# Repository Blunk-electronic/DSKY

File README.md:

# DSKY
is a I²C controlled 8 digit display and keypad unit

some images:

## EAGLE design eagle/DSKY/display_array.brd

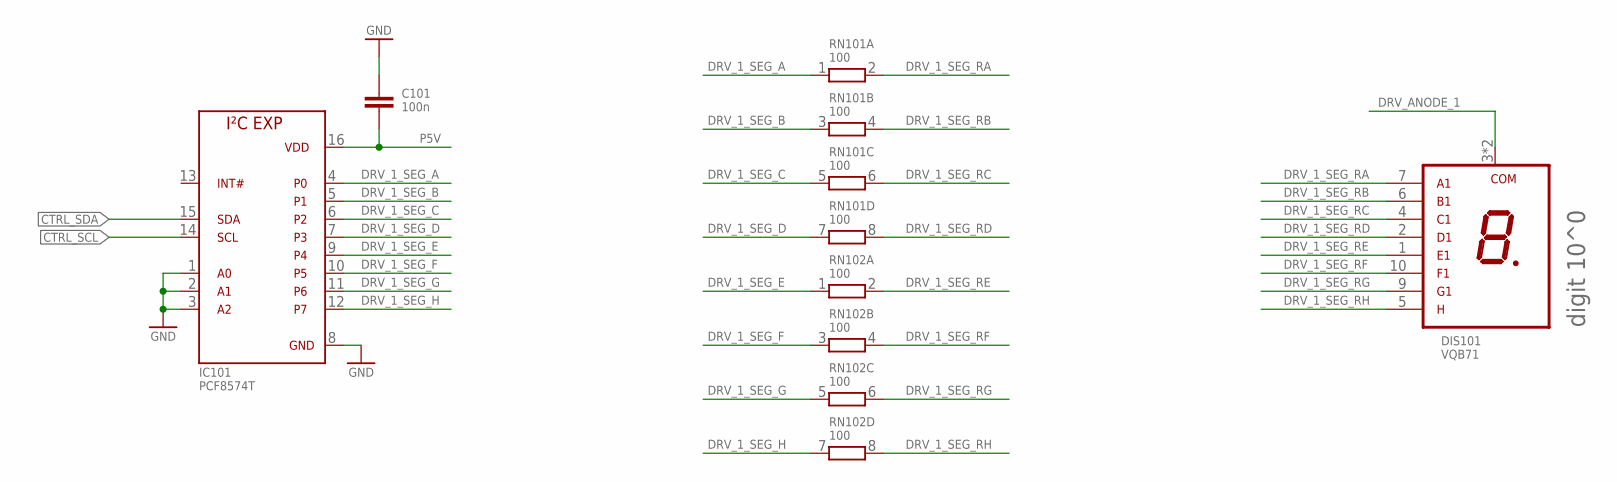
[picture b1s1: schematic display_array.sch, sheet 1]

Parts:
C101: 100n; S_0805; PART_CODE_BEL C_PAC_S_0805_VAL_100n
DIS101: VQB71; T_VQB71
IC101: PCF8574T; S_SOIC16
RN101, RN102: 100; T_SIL8; PART_CODE_BEL RN_PAC_T_SIL8_VAL_100

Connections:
CTRL_SCL: IC101.14 (SCL); also elsewhere on the board
CTRL_SDA: IC101.15 (SDA); also elsewhere on the board
DRV_1_SEG_A: IC101.4 (P0), RN101.1
DRV_1_SEG_B: IC101.5 (P1), RN101.3 (1)
DRV_1_SEG_C: IC101.6 (P2), RN101.5 (1)
DRV_1_SEG_D: IC101.7 (P3), RN101.7 (1)
DRV_1_SEG_E: IC101.9 (P4), RN102.1
DRV_1_SEG_F: IC101.10 (P5), RN102.3 (1)
DRV_1_SEG_G: IC101.11 (P6), RN102.5 (1)
DRV_1_SEG_H: IC101.12 (P7), RN102.7 (1)
DRV_1_SEG_RA: DIS101.7 (A1), RN101.2
DRV_1_SEG_RB: DIS101.6 (B1), RN101.4 (2)
DRV_1_SEG_RC: DIS101.4 (C1), RN101.6 (2)
DRV_1_SEG_RD: DIS101.2 (D1), RN101.8 (2)
DRV_1_SEG_RE: DIS101.1 (E1), RN102.2
DRV_1_SEG_RF: DIS101.10 (F1), RN102.4 (2)
DRV_1_SEG_RG: DIS101.9 (G1), RN102.6 (2)
DRV_1_SEG_RH: DIS101.5 (DP1), RN102.8 (2)
DRV_ANODE_1: DIS101.3 (COM1), DIS101.8 (COM1); also elsewhere on the board
GND: C101.1, IC101.1 (A0), IC101.2 (A1), IC101.3 (A2), IC101.8 (GND); also elsewhere on the board
P5V: C101.2, IC101.16 (VDD); also elsewhere on the board

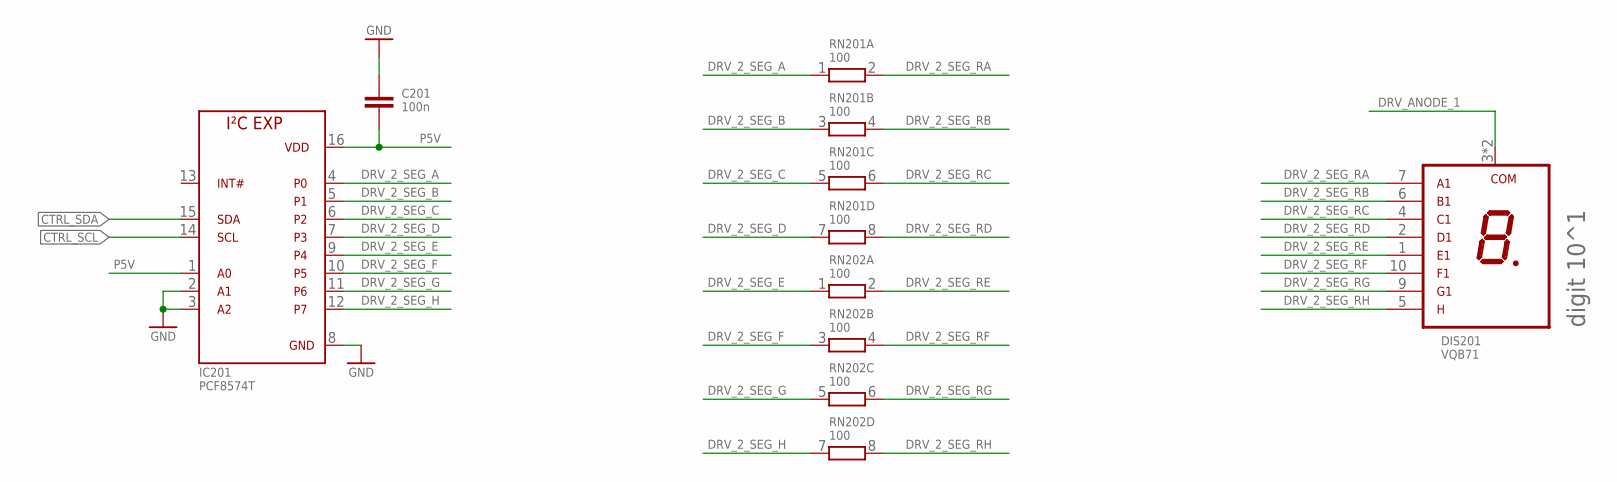
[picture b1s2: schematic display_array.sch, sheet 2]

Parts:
C201: 100n; S_0805; PART_CODE_BEL C_PAC_S_0805_VAL_100n
DIS201: VQB71; T_VQB71
IC201: PCF8574T; S_SOIC16
RN201, RN202: 100; T_SIL8; PART_CODE_BEL RN_PAC_T_SIL8_VAL_100

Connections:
CTRL_SCL: IC201.14 (SCL); also elsewhere on the board
CTRL_SDA: IC201.15 (SDA); also elsewhere on the board
DRV_2_SEG_A: IC201.4 (P0), RN201.1
DRV_2_SEG_B: IC201.5 (P1), RN201.3 (1)
DRV_2_SEG_C: IC201.6 (P2), RN201.5 (1)
DRV_2_SEG_D: IC201.7 (P3), RN201.7 (1)
DRV_2_SEG_E: IC201.9 (P4), RN202.1
DRV_2_SEG_F: IC201.10 (P5), RN202.3 (1)
DRV_2_SEG_G: IC201.11 (P6), RN202.5 (1)
DRV_2_SEG_H: IC201.12 (P7), RN202.7 (1)
DRV_2_SEG_RA: DIS201.7 (A1), RN201.2
DRV_2_SEG_RB: DIS201.6 (B1), RN201.4 (2)
DRV_2_SEG_RC: DIS201.4 (C1), RN201.6 (2)
DRV_2_SEG_RD: DIS201.2 (D1), RN201.8 (2)
DRV_2_SEG_RE: DIS201.1 (E1), RN202.2
DRV_2_SEG_RF: DIS201.10 (F1), RN202.4 (2)
DRV_2_SEG_RG: DIS201.9 (G1), RN202.6 (2)
DRV_2_SEG_RH: DIS201.5 (DP1), RN202.8 (2)
DRV_ANODE_1: DIS201.3 (COM1), DIS201.8 (COM1); also elsewhere on the board
GND: C201.1, IC201.2 (A1), IC201.3 (A2), IC201.8 (GND); also elsewhere on the board
P5V: C201.2, IC201.1 (A0), IC201.16 (VDD); also elsewhere on the board

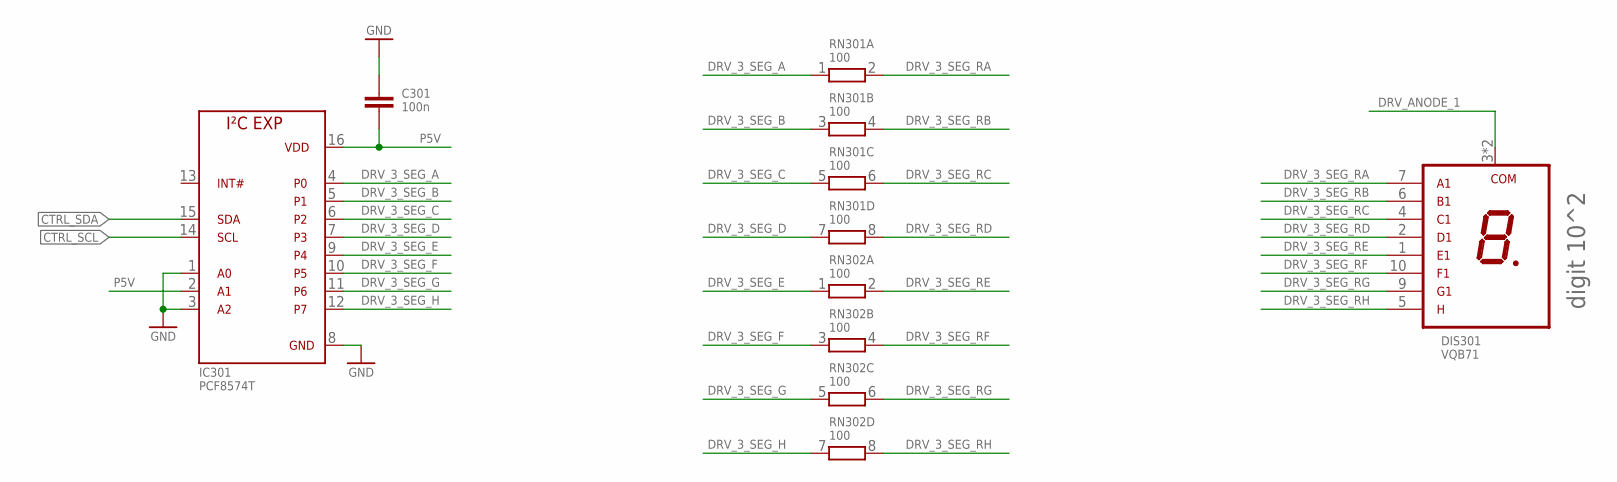
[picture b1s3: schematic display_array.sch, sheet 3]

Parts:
C301: 100n; S_0805; PART_CODE_BEL C_PAC_S_0805_VAL_100n
DIS301: VQB71; T_VQB71
IC301: PCF8574T; S_SOIC16
RN301, RN302: 100; T_SIL8; PART_CODE_BEL RN_PAC_T_SIL8_VAL_100

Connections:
CTRL_SCL: IC301.14 (SCL); also elsewhere on the board
CTRL_SDA: IC301.15 (SDA); also elsewhere on the board
DRV_3_SEG_A: IC301.4 (P0), RN301.1
DRV_3_SEG_B: IC301.5 (P1), RN301.3 (1)
DRV_3_SEG_C: IC301.6 (P2), RN301.5 (1)
DRV_3_SEG_D: IC301.7 (P3), RN301.7 (1)
DRV_3_SEG_E: IC301.9 (P4), RN302.1
DRV_3_SEG_F: IC301.10 (P5), RN302.3 (1)
DRV_3_SEG_G: IC301.11 (P6), RN302.5 (1)
DRV_3_SEG_H: IC301.12 (P7), RN302.7 (1)
DRV_3_SEG_RA: DIS301.7 (A1), RN301.2
DRV_3_SEG_RB: DIS301.6 (B1), RN301.4 (2)
DRV_3_SEG_RC: DIS301.4 (C1), RN301.6 (2)
DRV_3_SEG_RD: DIS301.2 (D1), RN301.8 (2)
DRV_3_SEG_RE: DIS301.1 (E1), RN302.2
DRV_3_SEG_RF: DIS301.10 (F1), RN302.4 (2)
DRV_3_SEG_RG: DIS301.9 (G1), RN302.6 (2)
DRV_3_SEG_RH: DIS301.5 (DP1), RN302.8 (2)
DRV_ANODE_1: DIS301.3 (COM1), DIS301.8 (COM1); also elsewhere on the board
GND: C301.1, IC301.1 (A0), IC301.3 (A2), IC301.8 (GND); also elsewhere on the board
P5V: C301.2, IC301.2 (A1), IC301.16 (VDD); also elsewhere on the board

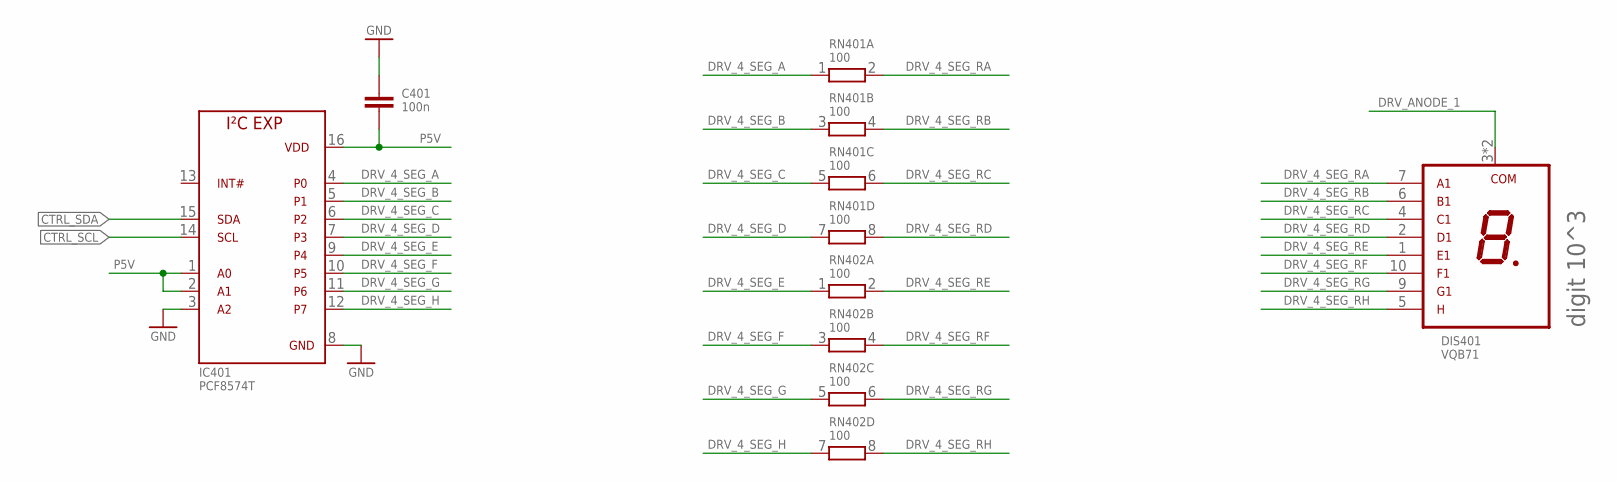
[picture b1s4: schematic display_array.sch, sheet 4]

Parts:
C401: 100n; S_0805; PART_CODE_BEL C_PAC_S_0805_VAL_100n
DIS401: VQB71; T_VQB71
IC401: PCF8574T; S_SOIC16
RN401, RN402: 100; T_SIL8; PART_CODE_BEL RN_PAC_T_SIL8_VAL_100

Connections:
CTRL_SCL: IC401.14 (SCL); also elsewhere on the board
CTRL_SDA: IC401.15 (SDA); also elsewhere on the board
DRV_4_SEG_A: IC401.4 (P0), RN401.1
DRV_4_SEG_B: IC401.5 (P1), RN401.3 (1)
DRV_4_SEG_C: IC401.6 (P2), RN401.5 (1)
DRV_4_SEG_D: IC401.7 (P3), RN401.7 (1)
DRV_4_SEG_E: IC401.9 (P4), RN402.1
DRV_4_SEG_F: IC401.10 (P5), RN402.3 (1)
DRV_4_SEG_G: IC401.11 (P6), RN402.5 (1)
DRV_4_SEG_H: IC401.12 (P7), RN402.7 (1)
DRV_4_SEG_RA: DIS401.7 (A1), RN401.2
DRV_4_SEG_RB: DIS401.6 (B1), RN401.4 (2)
DRV_4_SEG_RC: DIS401.4 (C1), RN401.6 (2)
DRV_4_SEG_RD: DIS401.2 (D1), RN401.8 (2)
DRV_4_SEG_RE: DIS401.1 (E1), RN402.2
DRV_4_SEG_RF: DIS401.10 (F1), RN402.4 (2)
DRV_4_SEG_RG: DIS401.9 (G1), RN402.6 (2)
DRV_4_SEG_RH: DIS401.5 (DP1), RN402.8 (2)
DRV_ANODE_1: DIS401.3 (COM1), DIS401.8 (COM1); also elsewhere on the board
GND: C401.1, IC401.3 (A2), IC401.8 (GND); also elsewhere on the board
P5V: C401.2, IC401.1 (A0), IC401.2 (A1), IC401.16 (VDD); also elsewhere on the board

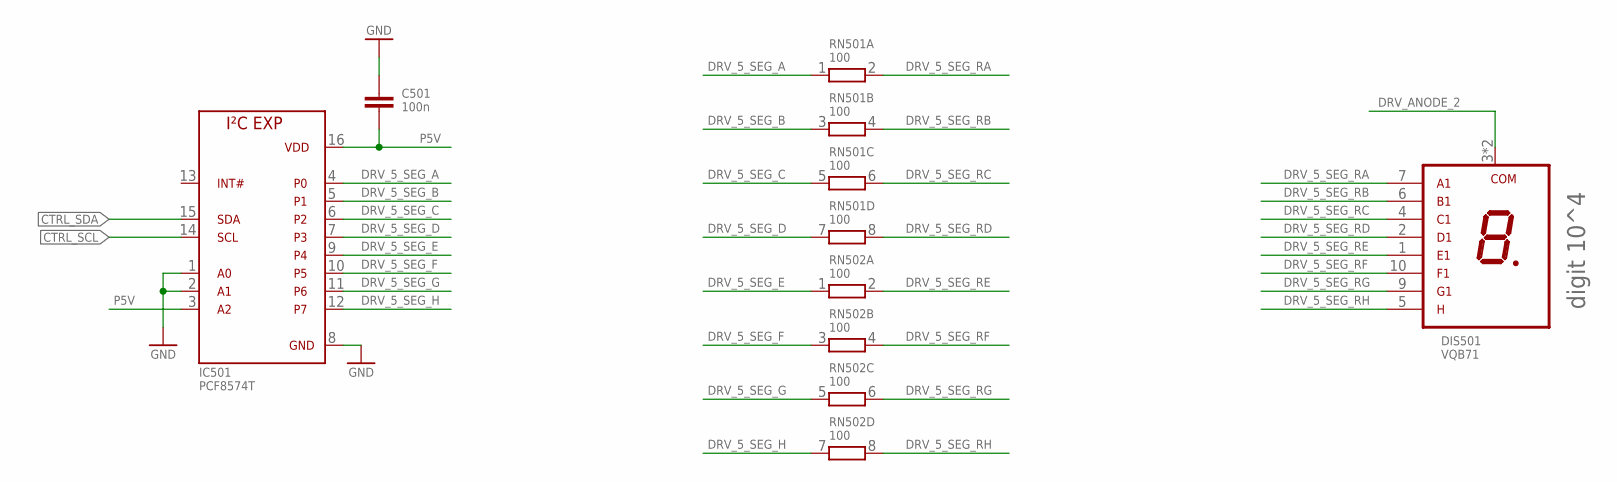
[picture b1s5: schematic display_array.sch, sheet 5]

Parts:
C501: 100n; S_0805; PART_CODE_BEL C_PAC_S_0805_VAL_100n
DIS501: VQB71; T_VQB71
IC501: PCF8574T; S_SOIC16
RN501, RN502: 100; T_SIL8; PART_CODE_BEL RN_PAC_T_SIL8_VAL_100

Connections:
CTRL_SCL: IC501.14 (SCL); also elsewhere on the board
CTRL_SDA: IC501.15 (SDA); also elsewhere on the board
DRV_5_SEG_A: IC501.4 (P0), RN501.1
DRV_5_SEG_B: IC501.5 (P1), RN501.3 (1)
DRV_5_SEG_C: IC501.6 (P2), RN501.5 (1)
DRV_5_SEG_D: IC501.7 (P3), RN501.7 (1)
DRV_5_SEG_E: IC501.9 (P4), RN502.1
DRV_5_SEG_F: IC501.10 (P5), RN502.3 (1)
DRV_5_SEG_G: IC501.11 (P6), RN502.5 (1)
DRV_5_SEG_H: IC501.12 (P7), RN502.7 (1)
DRV_5_SEG_RA: DIS501.7 (A1), RN501.2
DRV_5_SEG_RB: DIS501.6 (B1), RN501.4 (2)
DRV_5_SEG_RC: DIS501.4 (C1), RN501.6 (2)
DRV_5_SEG_RD: DIS501.2 (D1), RN501.8 (2)
DRV_5_SEG_RE: DIS501.1 (E1), RN502.2
DRV_5_SEG_RF: DIS501.10 (F1), RN502.4 (2)
DRV_5_SEG_RG: DIS501.9 (G1), RN502.6 (2)
DRV_5_SEG_RH: DIS501.5 (DP1), RN502.8 (2)
DRV_ANODE_2: DIS501.3 (COM1), DIS501.8 (COM1); also elsewhere on the board
GND: C501.1, IC501.1 (A0), IC501.2 (A1), IC501.8 (GND); also elsewhere on the board
P5V: C501.2, IC501.3 (A2), IC501.16 (VDD); also elsewhere on the board

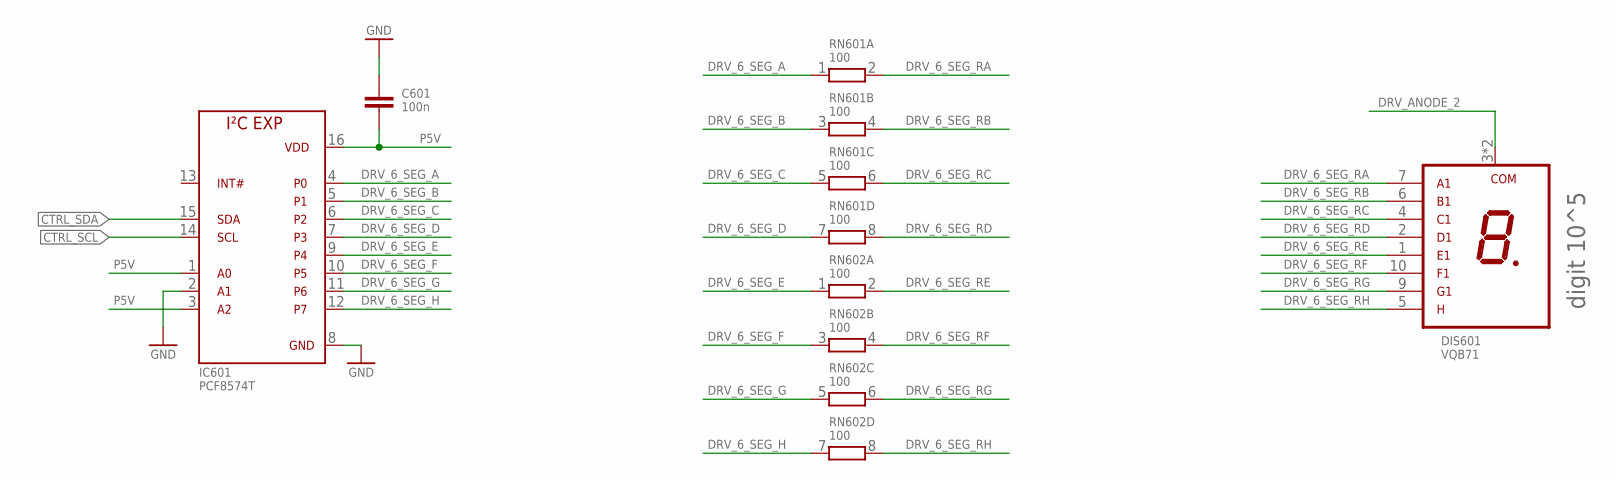
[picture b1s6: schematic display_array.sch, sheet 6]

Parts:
C601: 100n; S_0805; PART_CODE_BEL C_PAC_S_0805_VAL_100n
DIS601: VQB71; T_VQB71
IC601: PCF8574T; S_SOIC16
RN601, RN602: 100; T_SIL8; PART_CODE_BEL RN_PAC_T_SIL8_VAL_100

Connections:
CTRL_SCL: IC601.14 (SCL); also elsewhere on the board
CTRL_SDA: IC601.15 (SDA); also elsewhere on the board
DRV_6_SEG_A: IC601.4 (P0), RN601.1
DRV_6_SEG_B: IC601.5 (P1), RN601.3 (1)
DRV_6_SEG_C: IC601.6 (P2), RN601.5 (1)
DRV_6_SEG_D: IC601.7 (P3), RN601.7 (1)
DRV_6_SEG_E: IC601.9 (P4), RN602.1
DRV_6_SEG_F: IC601.10 (P5), RN602.3 (1)
DRV_6_SEG_G: IC601.11 (P6), RN602.5 (1)
DRV_6_SEG_H: IC601.12 (P7), RN602.7 (1)
DRV_6_SEG_RA: DIS601.7 (A1), RN601.2
DRV_6_SEG_RB: DIS601.6 (B1), RN601.4 (2)
DRV_6_SEG_RC: DIS601.4 (C1), RN601.6 (2)
DRV_6_SEG_RD: DIS601.2 (D1), RN601.8 (2)
DRV_6_SEG_RE: DIS601.1 (E1), RN602.2
DRV_6_SEG_RF: DIS601.10 (F1), RN602.4 (2)
DRV_6_SEG_RG: DIS601.9 (G1), RN602.6 (2)
DRV_6_SEG_RH: DIS601.5 (DP1), RN602.8 (2)
DRV_ANODE_2: DIS601.3 (COM1), DIS601.8 (COM1); also elsewhere on the board
GND: C601.1, IC601.2 (A1), IC601.8 (GND); also elsewhere on the board
P5V: C601.2, IC601.1 (A0), IC601.3 (A2), IC601.16 (VDD); also elsewhere on the board

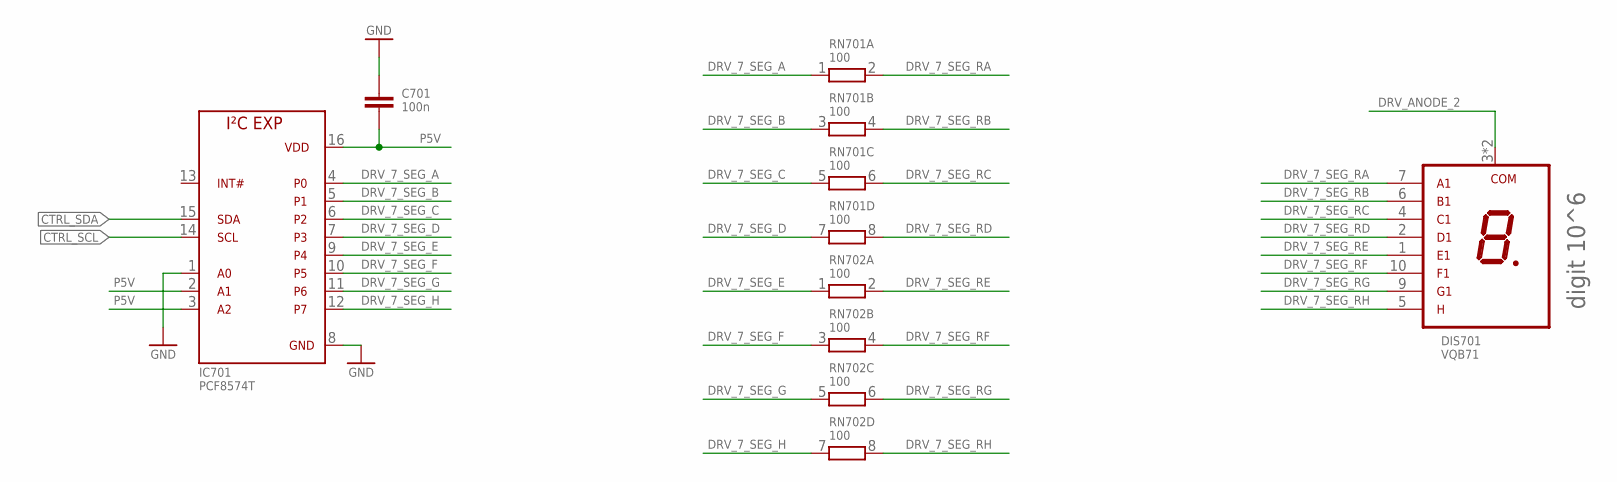
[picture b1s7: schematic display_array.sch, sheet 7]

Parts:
C701: 100n; S_0805; PART_CODE_BEL C_PAC_S_0805_VAL_100n
DIS701: VQB71; T_VQB71
IC701: PCF8574T; S_SOIC16
RN701, RN702: 100; T_SIL8; PART_CODE_BEL RN_PAC_T_SIL8_VAL_100

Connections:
CTRL_SCL: IC701.14 (SCL); also elsewhere on the board
CTRL_SDA: IC701.15 (SDA); also elsewhere on the board
DRV_7_SEG_A: IC701.4 (P0), RN701.1
DRV_7_SEG_B: IC701.5 (P1), RN701.3 (1)
DRV_7_SEG_C: IC701.6 (P2), RN701.5 (1)
DRV_7_SEG_D: IC701.7 (P3), RN701.7 (1)
DRV_7_SEG_E: IC701.9 (P4), RN702.1
DRV_7_SEG_F: IC701.10 (P5), RN702.3 (1)
DRV_7_SEG_G: IC701.11 (P6), RN702.5 (1)
DRV_7_SEG_H: IC701.12 (P7), RN702.7 (1)
DRV_7_SEG_RA: DIS701.7 (A1), RN701.2
DRV_7_SEG_RB: DIS701.6 (B1), RN701.4 (2)
DRV_7_SEG_RC: DIS701.4 (C1), RN701.6 (2)
DRV_7_SEG_RD: DIS701.2 (D1), RN701.8 (2)
DRV_7_SEG_RE: DIS701.1 (E1), RN702.2
DRV_7_SEG_RF: DIS701.10 (F1), RN702.4 (2)
DRV_7_SEG_RG: DIS701.9 (G1), RN702.6 (2)
DRV_7_SEG_RH: DIS701.5 (DP1), RN702.8 (2)
DRV_ANODE_2: DIS701.3 (COM1), DIS701.8 (COM1); also elsewhere on the board
GND: C701.1, IC701.1 (A0), IC701.8 (GND); also elsewhere on the board
P5V: C701.2, IC701.2 (A1), IC701.3 (A2), IC701.16 (VDD); also elsewhere on the board

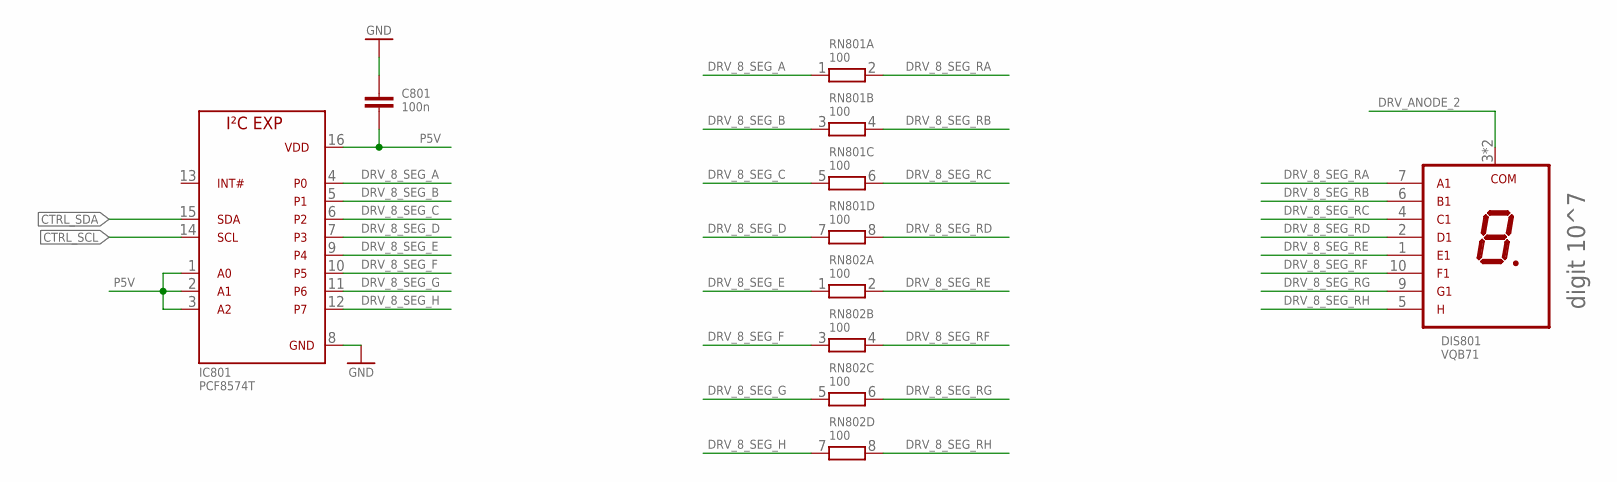
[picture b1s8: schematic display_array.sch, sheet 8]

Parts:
C801: 100n; S_0805; PART_CODE_BEL C_PAC_S_0805_VAL_100n
DIS801: VQB71; T_VQB71
IC801: PCF8574T; S_SOIC16
RN801, RN802: 100; T_SIL8; PART_CODE_BEL RN_PAC_T_SIL8_VAL_100

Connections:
CTRL_SCL: IC801.14 (SCL); also elsewhere on the board
CTRL_SDA: IC801.15 (SDA); also elsewhere on the board
DRV_8_SEG_A: IC801.4 (P0), RN801.1
DRV_8_SEG_B: IC801.5 (P1), RN801.3 (1)
DRV_8_SEG_C: IC801.6 (P2), RN801.5 (1)
DRV_8_SEG_D: IC801.7 (P3), RN801.7 (1)
DRV_8_SEG_E: IC801.9 (P4), RN802.1
DRV_8_SEG_F: IC801.10 (P5), RN802.3 (1)
DRV_8_SEG_G: IC801.11 (P6), RN802.5 (1)
DRV_8_SEG_H: IC801.12 (P7), RN802.7 (1)
DRV_8_SEG_RA: DIS801.7 (A1), RN801.2
DRV_8_SEG_RB: DIS801.6 (B1), RN801.4 (2)
DRV_8_SEG_RC: DIS801.4 (C1), RN801.6 (2)
DRV_8_SEG_RD: DIS801.2 (D1), RN801.8 (2)
DRV_8_SEG_RE: DIS801.1 (E1), RN802.2
DRV_8_SEG_RF: DIS801.10 (F1), RN802.4 (2)
DRV_8_SEG_RG: DIS801.9 (G1), RN802.6 (2)
DRV_8_SEG_RH: DIS801.5 (DP1), RN802.8 (2)
DRV_ANODE_2: DIS801.3 (COM1), DIS801.8 (COM1); also elsewhere on the board
GND: C801.1, IC801.8 (GND); also elsewhere on the board
P5V: C801.2, IC801.1 (A0), IC801.2 (A1), IC801.3 (A2), IC801.16 (VDD); also elsewhere on the board

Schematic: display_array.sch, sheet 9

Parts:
C901: 100n; S_0805; PART_CODE_BEL C_PAC_S_0805_VAL_100n
IC901: PCF8574AT; S_SOIC16; PART_CODE_BEL IC_PAC_S_SOIC16_VAL_PCF8574AT
LED901, LED902, LED903, LED908, LED911, LED912, LED913: red; S_0805; PART_CODE_BEL LED_PAC_S_0805_VAL_red
LED904, LED905: green; S_0805; PART_CODE_BEL LED_PAC_S_0805_VAL_green
LED906, LED907: yellow; S_0805; PART_CODE_BEL LED_PAC_S_0805_VAL_yellow
LED909, LED910: blue; S_0805; PART_CODE_BEL LED_PAC_S_0805_VAL_blue
R901, R902, R903: 1k5; S_0805; PART_CODE_BEL R_PAC_S_0805_VAL_1k5
R904, R905: 750; S_0805; PART_CODE_BEL R_PAC_S_0805_VAL_750
R906, R907: 2k2; S_0805; PART_CODE_BEL R_PAC_S_0805_VAL_2k2
R908: 3k3; S_0805; PART_CODE_BEL R_PAC_S_0805_VAL_3k3
R909, R910: 2k4; S_0805; PART_CODE_BEL R_PAC_S_0805_VAL_2k4

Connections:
CTRL_SCL: IC901.14 (SCL); also elsewhere on the board
CTRL_SDA: IC901.15 (SDA); also elsewhere on the board
DRV_9_LED_1: IC901.4 (P0), R901.1, R902.1, R903.1
DRV_9_LED_2: IC901.5 (P1), R904.1
DRV_9_LED_3: IC901.6 (P2), R905.1
DRV_9_LED_4: IC901.7 (P3), R906.1
DRV_9_LED_5: IC901.9 (P4), R907.1
DRV_9_LED_6: IC901.10 (P5), R908.1
DRV_9_LED_7: IC901.11 (P6), R909.1
DRV_9_LED_8: IC901.12 (P7), R910.1
DRV_9_LED_R1A: LED902.C, R902.2
DRV_9_LED_R1AA: LED902.A, LED912.C
DRV_9_LED_R1B: LED903.C, R903.2
DRV_9_LED_R1BB: LED903.A, LED913.C
DRV_9_LED_R1C: LED901.C, R901.2
DRV_9_LED_R1CC: LED901.A, LED911.C
DRV_9_LED_R2: LED904.C, R904.2
DRV_9_LED_R3: LED905.C, R905.2
DRV_9_LED_R4: LED906.C, R906.2
DRV_9_LED_R5: LED907.C, R907.2
DRV_9_LED_R6: LED908.C, R908.2
DRV_9_LED_R7: LED909.C, R909.2
DRV_9_LED_R8: LED910.C, R910.2
DRV_ANODE_1: LED904.A, LED905.A, LED906.A, LED907.A, LED908.A, LED909.A, LED910.A, LED911.A, LED912.A, LED913.A; also elsewhere on the board
GND: C901.1, IC901.1 (A0), IC901.2 (A1), IC901.3 (A2), IC901.8 (GND); also elsewhere on the board
P5V: C901.2, IC901.16 (VDD); also elsewhere on the board

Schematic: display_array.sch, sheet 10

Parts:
C1001: 100n; S_0805; PART_CODE_BEL C_PAC_S_0805_VAL_100n
IC1001: PCF8574AT; S_SOIC16; PART_CODE_BEL IC_PAC_S_SOIC16_VAL_PCF8574AT
RN1001, RN1002: 100; T_SIL8; PART_CODE_BEL RN_PAC_T_SIL8_VAL_100

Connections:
CTRL_SCL: IC1001.14 (SCL); also elsewhere on the board
CTRL_SDA: IC1001.15 (SDA); also elsewhere on the board
DEBOUNCER_1_OUT#: RN1001.2; also elsewhere on the board
DEBOUNCER_2_OUT#: RN1001.4 (2); also elsewhere on the board
DEBOUNCER_3_OUT#: RN1001.6 (2); also elsewhere on the board
DEBOUNCER_4_OUT#: RN1001.8 (2); also elsewhere on the board
DEBOUNCER_5_OUT#: RN1002.2; also elsewhere on the board
DEBOUNCER_6_OUT#: RN1002.4 (2); also elsewhere on the board
DEBOUNCER_7_OUT#: RN1002.6 (2); also elsewhere on the board
DEBOUNCER_8_OUT#: RN1002.8 (2); also elsewhere on the board
GND: C1001.1, IC1001.2 (A1), IC1001.3 (A2), IC1001.8 (GND); also elsewhere on the board
KEYPAD_1_K_1: IC1001.4 (P0), RN1001.1
KEYPAD_1_K_2: IC1001.5 (P1), RN1001.3 (1)
KEYPAD_1_K_3: IC1001.6 (P2), RN1001.5 (1)
KEYPAD_1_K_4: IC1001.7 (P3), RN1001.7 (1)
KEYPAD_1_K_5: IC1001.9 (P4), RN1002.1
KEYPAD_1_K_6: IC1001.10 (P5), RN1002.3 (1)
KEYPAD_1_K_7: IC1001.11 (P6), RN1002.5 (1)
KEYPAD_1_K_8: IC1001.12 (P7), RN1002.7 (1)
P5V: C1001.2, IC1001.1 (A0), IC1001.16 (VDD); also elsewhere on the board

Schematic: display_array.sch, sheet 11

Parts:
FD1101, FD1102: FIDUCIAL_CROSSHAIR; CROSSHAIR
H1101, H1102, H1103, H1104: HOLE_4.1_PAD; 4.1_PAD
TP1101, TP1102, TP1103, TP1104, TP1105, TP1106, TP1107, TP1108, TP1109, TP1110, TP1111, TP1112, TP1113, TP1114, TP1115, TP1116, TP1117, TP1118, TP1119, TP1120, TP1121, TP1122, TP1123, TP1124, TP1125, TP1126, TP1127: TEST_POINT_T_SMALL; T_TEST_POINT_SMALL

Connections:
GND: H1101.H1, H1102.H1, H1103.H1, H1104.H1; also elsewhere on the board

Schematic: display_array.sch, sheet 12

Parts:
C1201, C1202, C1203, C1204: 10u; T_RADIAL_5MM_GRID_2.54MM; PART_CODE_BEL C_PAC_T_RADIAL_5mm_GRID_2.54mm_VAL_10u_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
C1205, C1206: 100n; S_0805; PART_CODE_BEL C_PAC_S_0805_VAL_100n
IC1201, IC1202: SN7400N; T_NDIP14; PART_CODE_BEL IC_PAC_T_NDIP14_VAL_SN7400N
RN1201, RN1202: 220; T_SIL8; PART_CODE_BEL RN_PAC_T_SIL8_VAL_220
RN1203: 4k7; T_SIL8; PART_CODE_BEL RN_PAC_T_SIL8_VAL_4k7

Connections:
DEBOUNCER_1_OUT#: IC1201.6 (O), RN1203.4 (2); also elsewhere on the board
DEBOUNCER_2_OUT#: IC1201.8 (O), RN1203.2; also elsewhere on the board
DEBOUNCER_3_OUT#: IC1202.6 (O), RN1203.6 (2); also elsewhere on the board
DEBOUNCER_4_OUT#: IC1202.8 (O), RN1203.8 (2); also elsewhere on the board
DEBOUNCER_10: C1201.+, RN1201.2, RN1201.3 (1)
DEBOUNCER_11: IC1201.1 (I0), IC1201.2 (I1), RN1201.4 (2), RN1203.3 (1)
DEBOUNCER_12: IC1201.3 (O), IC1201.4 (I0), IC1201.5 (I1)
DEBOUNCER_20: C1202.+, RN1201.6 (2), RN1201.7 (1)
DEBOUNCER_21: IC1201.12 (I1), IC1201.13 (I0), RN1201.8 (2), RN1203.1
DEBOUNCER_22: IC1201.9 (I1), IC1201.10 (I0), IC1201.11 (O)
DEBOUNCER_30: C1203.+, RN1202.2, RN1202.3 (1)
DEBOUNCER_31: IC1202.1 (I0), IC1202.2 (I1), RN1202.4 (2), RN1203.5 (1)
DEBOUNCER_32: IC1202.3 (O), IC1202.4 (I0), IC1202.5 (I1)
DEBOUNCER_40: C1204.+, RN1202.6 (2), RN1202.7 (1)
DEBOUNCER_41: IC1202.12 (I1), IC1202.13 (I0), RN1202.8 (2), RN1203.7 (1)
DEBOUNCER_42: IC1202.9 (I1), IC1202.10 (I0), IC1202.11 (O)
GND: C1201.-, C1202.-, C1203.-, C1204.-, C1205.2, C1206.2, IC1201.7 (GND), IC1202.7 (GND); also elsewhere on the board
IN_1#: RN1201.1; also elsewhere on the board
IN_2#: RN1201.5 (1); also elsewhere on the board
IN_3#: RN1202.1; also elsewhere on the board
IN_4#: RN1202.5 (1); also elsewhere on the board
P5V: C1205.1, C1206.1, IC1201.14 (VCC), IC1202.14 (VCC); also elsewhere on the board

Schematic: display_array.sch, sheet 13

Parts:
C1301, C1302, C1303, C1304: 10u; T_RADIAL_5MM_GRID_2.54MM; PART_CODE_BEL C_PAC_T_RADIAL_5mm_GRID_2.54mm_VAL_10u_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
C1305, C1306: 100n; S_0805; PART_CODE_BEL C_PAC_S_0805_VAL_100n
IC1301, IC1302: SN7400N; T_NDIP14; PART_CODE_BEL IC_PAC_T_NDIP14_VAL_SN7400N
RN1301, RN1302: 220; T_SIL8; PART_CODE_BEL RN_PAC_T_SIL8_VAL_220
RN1303: 4k7; T_SIL8; PART_CODE_BEL RN_PAC_T_SIL8_VAL_4k7

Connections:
DEBOUNCER_5_OUT#: IC1301.6 (O), RN1303.4 (2); also elsewhere on the board
DEBOUNCER_6_OUT#: IC1301.8 (O), RN1303.2; also elsewhere on the board
DEBOUNCER_7_OUT#: IC1302.6 (O), RN1303.6 (2); also elsewhere on the board
DEBOUNCER_8_OUT#: IC1302.8 (O), RN1303.8 (2); also elsewhere on the board
DEBOUNCER_50: C1301.+, RN1301.2, RN1301.3 (1)
DEBOUNCER_51: IC1301.1 (I0), IC1301.2 (I1), RN1301.4 (2), RN1303.3 (1)
DEBOUNCER_52: IC1301.3 (O), IC1301.4 (I0), IC1301.5 (I1)
DEBOUNCER_60: C1302.+, RN1301.6 (2), RN1301.7 (1)
DEBOUNCER_61: IC1301.12 (I1), IC1301.13 (I0), RN1301.8 (2), RN1303.1
DEBOUNCER_62: IC1301.9 (I1), IC1301.10 (I0), IC1301.11 (O)
DEBOUNCER_70: C1303.+, RN1302.2, RN1302.3 (1)
DEBOUNCER_71: IC1302.1 (I0), IC1302.2 (I1), RN1302.4 (2), RN1303.5 (1)
DEBOUNCER_72: IC1302.3 (O), IC1302.4 (I0), IC1302.5 (I1)
DEBOUNCER_80: C1304.+, RN1302.6 (2), RN1302.7 (1)
DEBOUNCER_81: IC1302.12 (I1), IC1302.13 (I0), RN1302.8 (2), RN1303.7 (1)
DEBOUNCER_82: IC1302.9 (I1), IC1302.10 (I0), IC1302.11 (O)
GND: C1301.-, C1302.-, C1303.-, C1304.-, C1305.2, C1306.2, IC1301.7 (GND), IC1302.7 (GND); also elsewhere on the board
IN_5#: RN1301.1; also elsewhere on the board
IN_6#: RN1301.5 (1); also elsewhere on the board
IN_7#: RN1302.1; also elsewhere on the board
IN_8#: RN1302.5 (1); also elsewhere on the board
P5V: C1305.1, C1306.1, IC1301.14 (VCC), IC1302.14 (VCC); also elsewhere on the board

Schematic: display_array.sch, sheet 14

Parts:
C1401, C1402: 100u; T_RADIAL_7MM_GRID_2.54MM; PART_CODE_BEL C_PAC_T_RADIAL_7mm_GRID_2.54mm_VAL_100u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
D1401: 1N5400; T_DO201_GRID_18MM; PART_CODE_BEL D_PAC_T_DO201_GRID_18MM_VAL_1N5400
LED1401: green; S_0805; PART_CODE_BEL LED_PAC_S_0805_VAL_green
R1401: 220; S_0805; PART_CODE_BEL R_PAC_S_0805_VAL_220
RN1401, RN1402: 10k; T_SIL9
TP1401, TP1402: TEST_POINT_T_SMALL; T_TEST_POINT_SMALL
X1401: CLAMP_1X4-T-5MM; T_WIRE_CLAMP_1X4_5MM
X1402: MALE_2X13-T-VERTICAL_2.54MM; T_MALE_2X13_VERTICAL_GRID_2.54MM
X1403: MALE_1X3; T_MALE_3X1_VERTICAL

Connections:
CTRL_ACK#: RN1402.3, X1402.19
CTRL_B2: RN1401.4, X1402.7
CTRL_B3: RN1401.5, X1402.9
CTRL_B4: RN1401.6, X1402.11
CTRL_B5: RN1401.7, X1402.13
CTRL_B6: RN1401.8, X1402.15
CTRL_B7: RN1401.9, X1402.17
CTRL_BUSY: RN1402.4, X1402.21
CTRL_SCL: RN1401.2, TP1401.1, X1402.3; also elsewhere on the board
CTRL_SDA: RN1401.3, TP1402.1, X1402.5; also elsewhere on the board
CTRL_STROBE#: RN1402.2, X1402.1
DRV_ANODE_2: LED1401.A; also elsewhere on the board
GND: C1401.-, C1402.-, D1401.A, R1401.1, X1401.3, X1401.4, X1402.2, X1402.4, X1402.6, X1402.8, X1402.10, X1402.12, X1402.14, X1402.16, X1402.18, X1402.20, X1402.22, X1402.24, X1402.26, X1403.1; also elsewhere on the board
P5V: C1401.+, C1402.+, D1401.C, RN1401.1, RN1402.1, X1401.1, X1401.2, X1403.3; also elsewhere on the board
P5V_LED: LED1401.C, R1401.2

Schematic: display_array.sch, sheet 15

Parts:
S1501, S1502, S1503, S1504, S1505, S1506, S1507, S1508: set; T_PUSH_BUTTON_6X6
X1501: MALE_2X13-T-VERTICAL_2.54MM; T_MALE_2X13_VERTICAL_GRID_2.54MM

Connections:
GND: S1501.1 (A1), S1501.3 (A1), S1502.1 (A1), S1502.3 (A1), S1503.1 (A1), S1503.3 (A1), S1504.1 (A1), S1504.3 (A1), S1505.1 (A1), S1505.3 (A1), S1506.1 (A1), S1506.3 (A1), S1507.1 (A1), S1507.3 (A1), S1508.1 (A1), S1508.3 (A1), X1501.2, X1501.4, X1501.6, X1501.8, X1501.10, X1501.12, X1501.14, X1501.16, X1501.18, X1501.20, X1501.22, X1501.24, X1501.26; also elsewhere on the board
IN_1#: S1501.2 (B1), S1501.4 (B1), X1501.3; also elsewhere on the board
IN_2#: S1502.2 (B1), S1502.4 (B1), X1501.5; also elsewhere on the board
IN_3#: S1503.2 (B1), S1503.4 (B1), X1501.7; also elsewhere on the board
IN_4#: S1504.2 (B1), S1504.4 (B1), X1501.9; also elsewhere on the board
IN_5#: S1505.2 (B1), S1505.4 (B1), X1501.11; also elsewhere on the board
IN_6#: S1506.2 (B1), S1506.4 (B1), X1501.13; also elsewhere on the board
IN_7#: S1507.2 (B1), S1507.4 (B1), X1501.15; also elsewhere on the board
IN_8#: S1508.2 (B1), S1508.4 (B1), X1501.17; also elsewhere on the board

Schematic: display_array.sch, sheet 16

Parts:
C1601, C1602, C1603: 100n; S_0805; PART_CODE_BEL C_PAC_S_0805_VAL_100n
C1604: 10n; S_0805; PART_CODE_BEL C_PAC_S_0805_VAL_10n
D1601: BAT48; T_DO204_GRID_10MM; PART_CODE_BEL D_PAC_T_DO204_GRID_10mm_VAL_BAT48
IC1601: NE555V; T_NDIP8; PART_CODE_BEL IC_PAC_T_NDIP8_VAL_NE555V
R1601: 10k; S_0805; PART_CODE_BEL R_PAC_S_0805_VAL_10k
R1602: 470k; S_0805; PART_CODE_BEL R_PAC_S_0805_VAL_470k
R1603: 1k; S_0805; PART_CODE_BEL R_PAC_S_0805_VAL_1k
T1601, T1602: NX2301P; S_SOT23; PART_CODE_BEL T_PAC_S_SOT23_VAL_NX2301P
TP1601, TP1602, TP1603, TP1604, TP1607: TEST_POINT_T_SMALL; T_TEST_POINT_SMALL
TP1605, TP1606: TEST_POINT_T_LARGE; T_TEST_POINT_LARGE

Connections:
DRV_ANODE_1: T1601.3 (D); also elsewhere on the board
DRV_ANODE_2: T1602.3 (D); also elsewhere on the board
GND: C1601.2, C1603.2, C1604.2, IC1601.1 (GND), TP1603.1; also elsewhere on the board
P5V: C1601.1, IC1601.8 (VCC), R1602.2, R1603.2, T1601.2 (S), T1602.2 (S), TP1602.1, TP1605.1; also elsewhere on the board
TIM_1: C1604.1, IC1601.4 (RST#), IC1601.5 (OC), TP1604.1
TIM_2: C1602.1, D1601.C, IC1601.2 (TRG), IC1601.6 (TRSHLD), R1601.1, TP1601.1
TIM_3: D1601.A, IC1601.7 (DSCHRG), R1601.2, R1602.1, TP1606.1
TIM_45: C1602.2, C1603.1
TIM_OUT: IC1601.3 (OUT), R1603.1, T1601.1 (G), T1602.1 (G), TP1607.1

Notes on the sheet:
LDC terminals

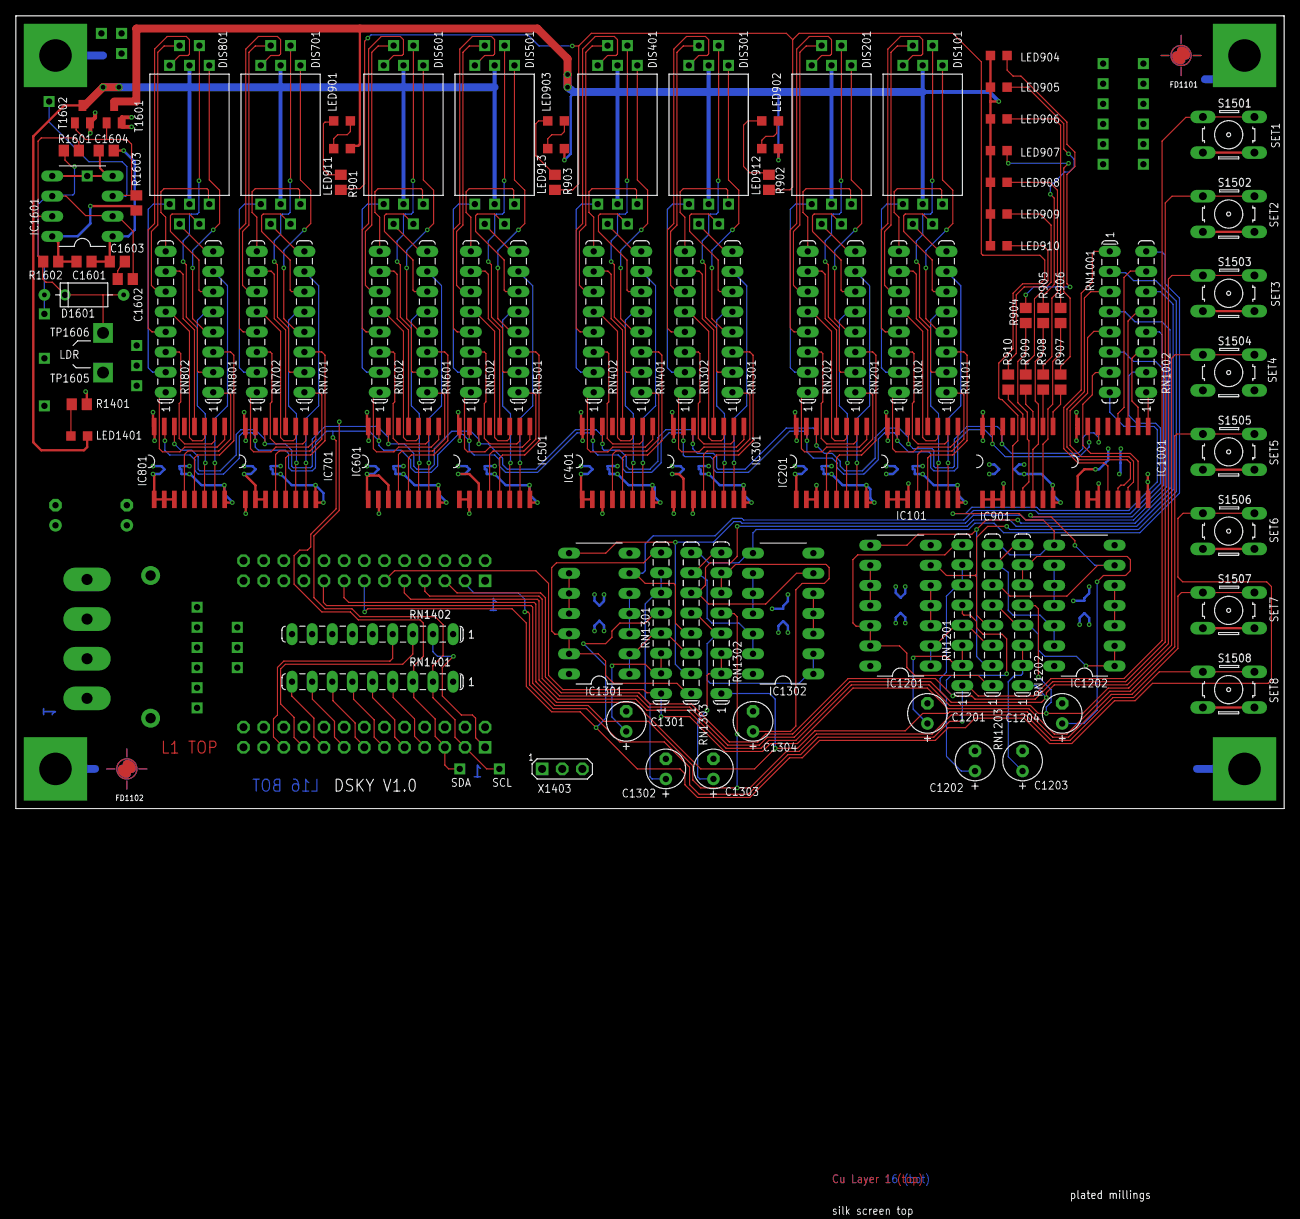
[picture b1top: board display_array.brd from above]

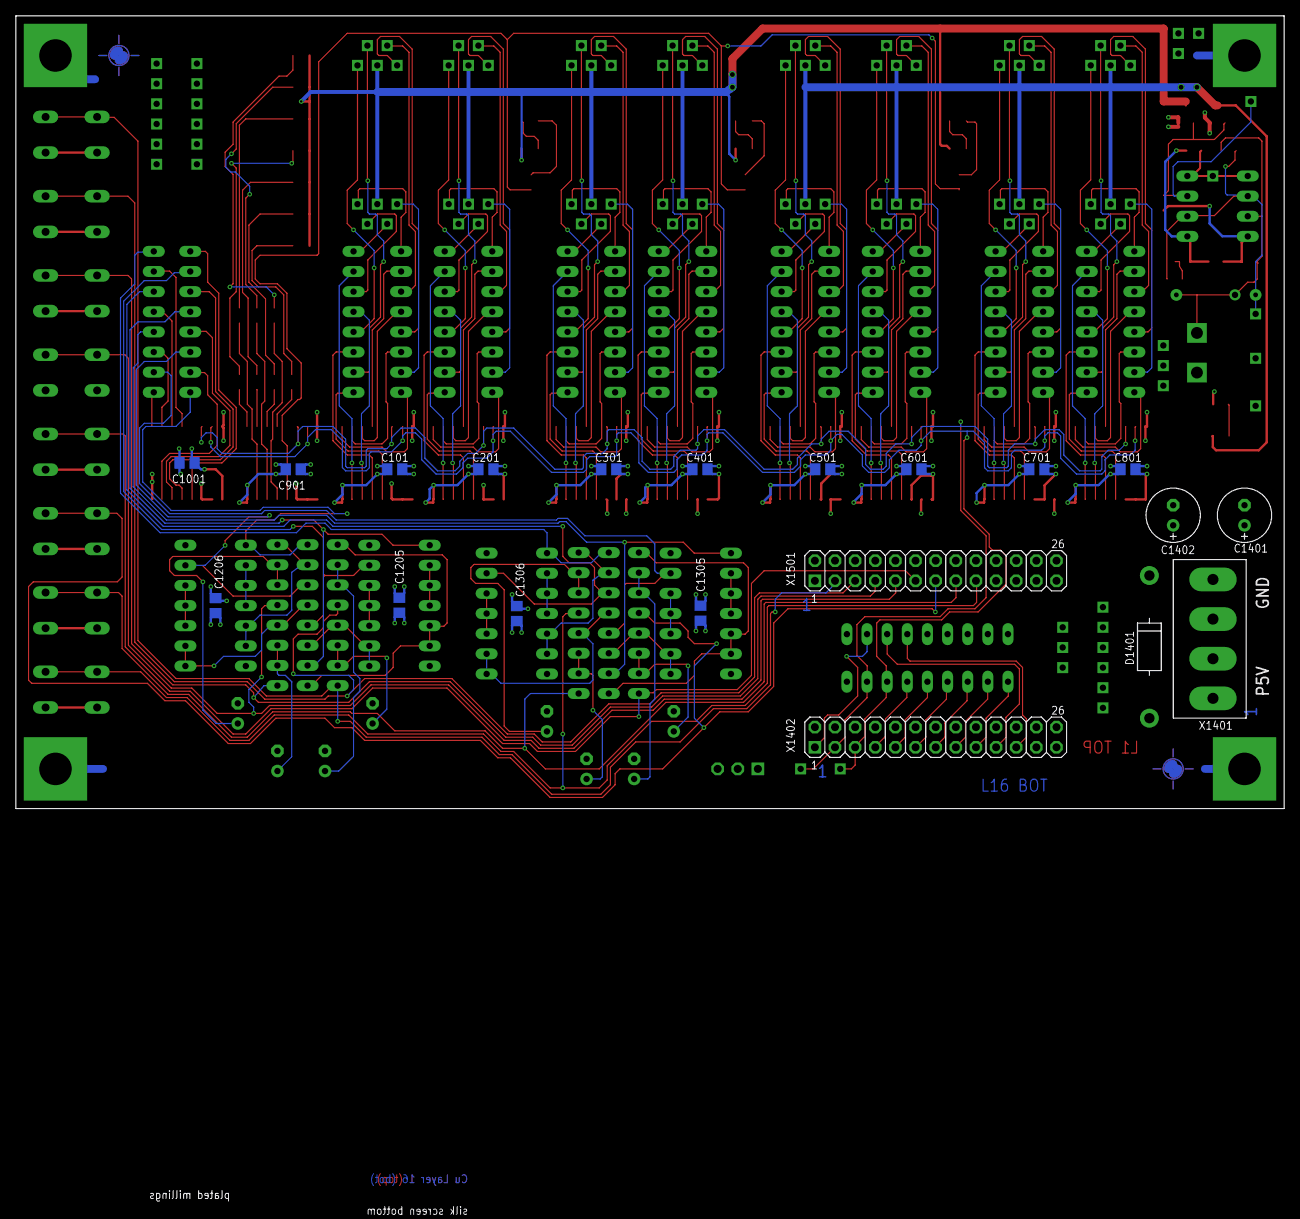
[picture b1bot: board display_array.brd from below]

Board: 4 copper layers, 160.0 x 149.8 mm, 164 parts (20 on the bottom side), 218 nets.

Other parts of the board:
U$1: A4_LANDSCAPE

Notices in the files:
parts and their libraries:
be_frame: Copyright(C) Blunk electronic
